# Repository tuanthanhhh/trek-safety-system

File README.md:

# Outdoor Safety Tracker System
> A Personal Outdoor Safety Tracker designed for trekking and remote activities, featuring fall detection, GPS tracking, environmental sensing, and LoRa-based emergency communication for real-time user monitoring.

## 📌 Overview
This project implements a handheld embedded system that enhances user safety during outdoor activities such as trekking, hiking, or exploration in remote areas.

The system continuously monitors user status and environment, detects abnormal conditions (e.g., fall or unconsciousness), and transmits alerts to a central monitoring station via LoRa communication.

## 🎯 Key Features
- Fall detection
- Lora Communication
- GPS Tracking
- Environmental Monitoring
- Digital Compass
- Emergency SOS

## 🏗️ System Architecture
🚧 Work in progress

## 🔧 Hardware Components
🚧 Work in progress
## 🧠 Software Design

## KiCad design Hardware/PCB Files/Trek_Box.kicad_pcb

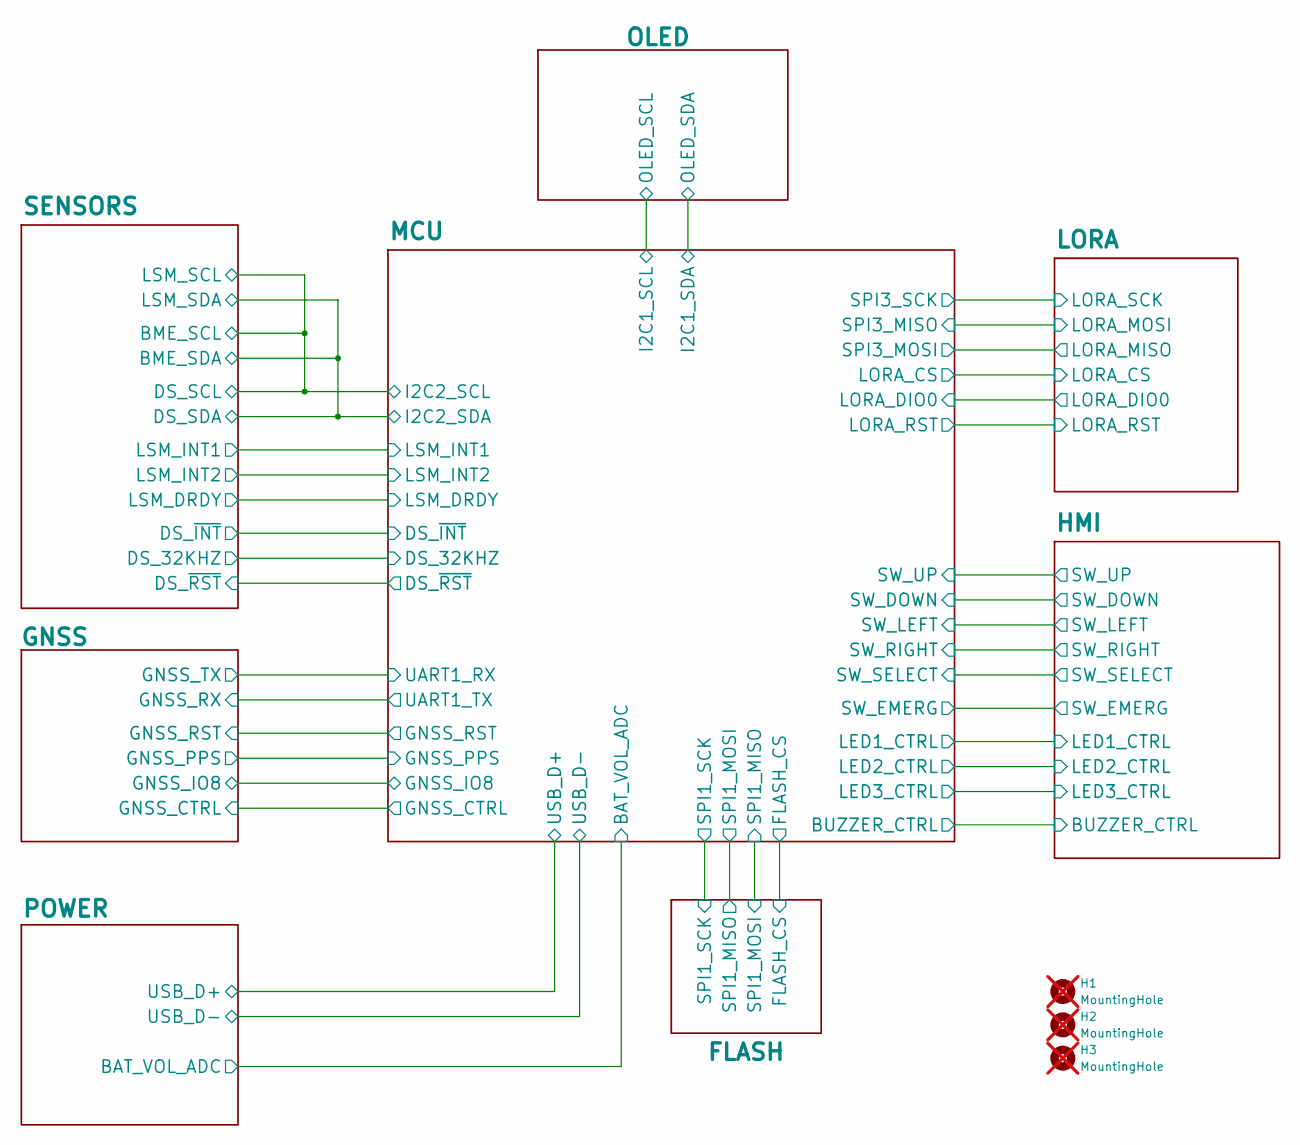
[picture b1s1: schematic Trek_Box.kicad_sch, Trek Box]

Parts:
H1, H2, H3: MountingHole; MountingHole_2.5mm; not fitted

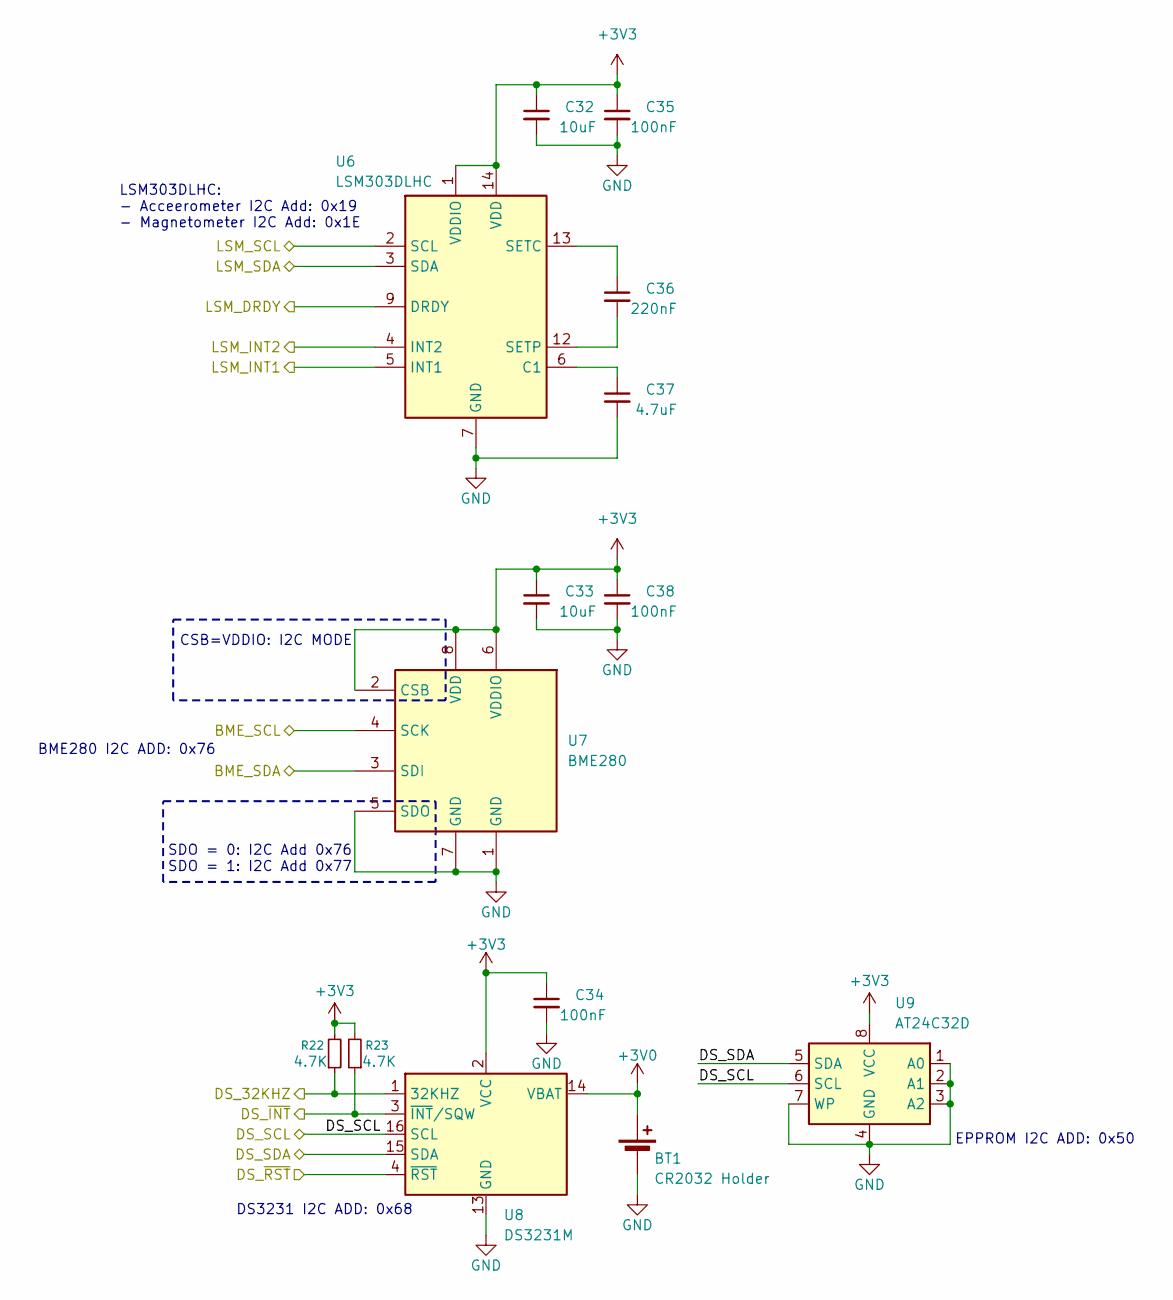
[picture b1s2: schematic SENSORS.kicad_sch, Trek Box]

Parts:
BT1: CR2032 Holder; BatteryHolder_Keystone_1060_1x2032
C32, C33: 10uF; C_0603_1608Metric; JLC C19702
C34, C35, C38: 100nF; C_0603_1608Metric; JLC C19702
C36: 220nF; C_0603_1608Metric; JLC C19702
C37: 4.7uF; C_0603_1608Metric; JLC C19702
R22, R23: 4.7K; R_0603_1608Metric
U6: LSM303DLHC; LGA-14_3x5mm_P0.8mm_LayoutBorder1x6y
U7: BME280; Bosch_LGA-8_2.5x2.5mm_P0.65mm_ClockwisePinNumbering
U8: DS3231M; SOIC-16W_7.5x10.3mm_P1.27mm
U9: AT24C32D; SOIC-8_3.9x4.9mm_P1.27mm

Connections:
+3V0: BT1.1 (+), U8.14 (VBAT); also elsewhere on the board
+3V3: C32.1, C33.1, C34.1, C35.1, C38.1, R22.2, R23.2, U6.1 (VDDIO), U6.14 (VDD), U7.2 (CSB), U7.6 (VDDIO), U7.8 (VDD), U8.2 (VCC), U9.8 (VCC); also elsewhere on the board
/MCU/DS_32KHZ: R22.1, U8.1 (32KHZ); also elsewhere on the board
/MCU/DS_~INT: R23.1, U8.3 (~INT/SQW); also elsewhere on the board
/MCU/DS_~RST: U8.4 (~RST); also elsewhere on the board
/MCU/I2C2_SCL: U6.2 (SCL), U7.4 (SCK), U8.16 (SCL), U9.6 (SCL); also elsewhere on the board
/MCU/I2C2_SDA: U6.3 (SDA), U7.3 (SDI), U8.15 (SDA), U9.5 (SDA); also elsewhere on the board
/MCU/LSM_DRDY: U6.9 (DRDY); also elsewhere on the board
/MCU/LSM_INT1: U6.5 (INT1); also elsewhere on the board
/MCU/LSM_INT2: U6.4 (INT2); also elsewhere on the board
GND: BT1.2 (-), C32.2, C33.2, C34.2, C35.2, C37.2, C38.2, U6.7 (GND), U6.10 (GND), U6.11 (GND), U7.1 (GND), U7.5 (SDO), U7.7 (GND), U8.5 (GND), U8.6 (GND), U8.7 (GND), U8.8 (GND), U8.9 (GND), U8.10 (GND), U8.11 (GND), U8.12 (GND), U8.13 (GND), U9.1 (A0), U9.2 (A1), U9.3 (A2), U9.4 (GND), U9.7 (WP); also elsewhere on the board
unnamed: C37.1, U6.6 (C1)
unnamed: C36.1, U6.13 (SETC)
unnamed: C36.2, U6.12 (SETP)

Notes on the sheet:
BME280 I2C ADD: 0x76
LSM303DLHC: - Acceerometer I2C Add: 0x19 - Magnetometer I2C Add: 0x1E
DS3231 I2C ADD: 0x68
SDO = 0: I2C Add 0x76 SDO = 1: I2C Add 0x77
CSB=VDDIO: I2C MODE
EPPROM I2C ADD: 0x50

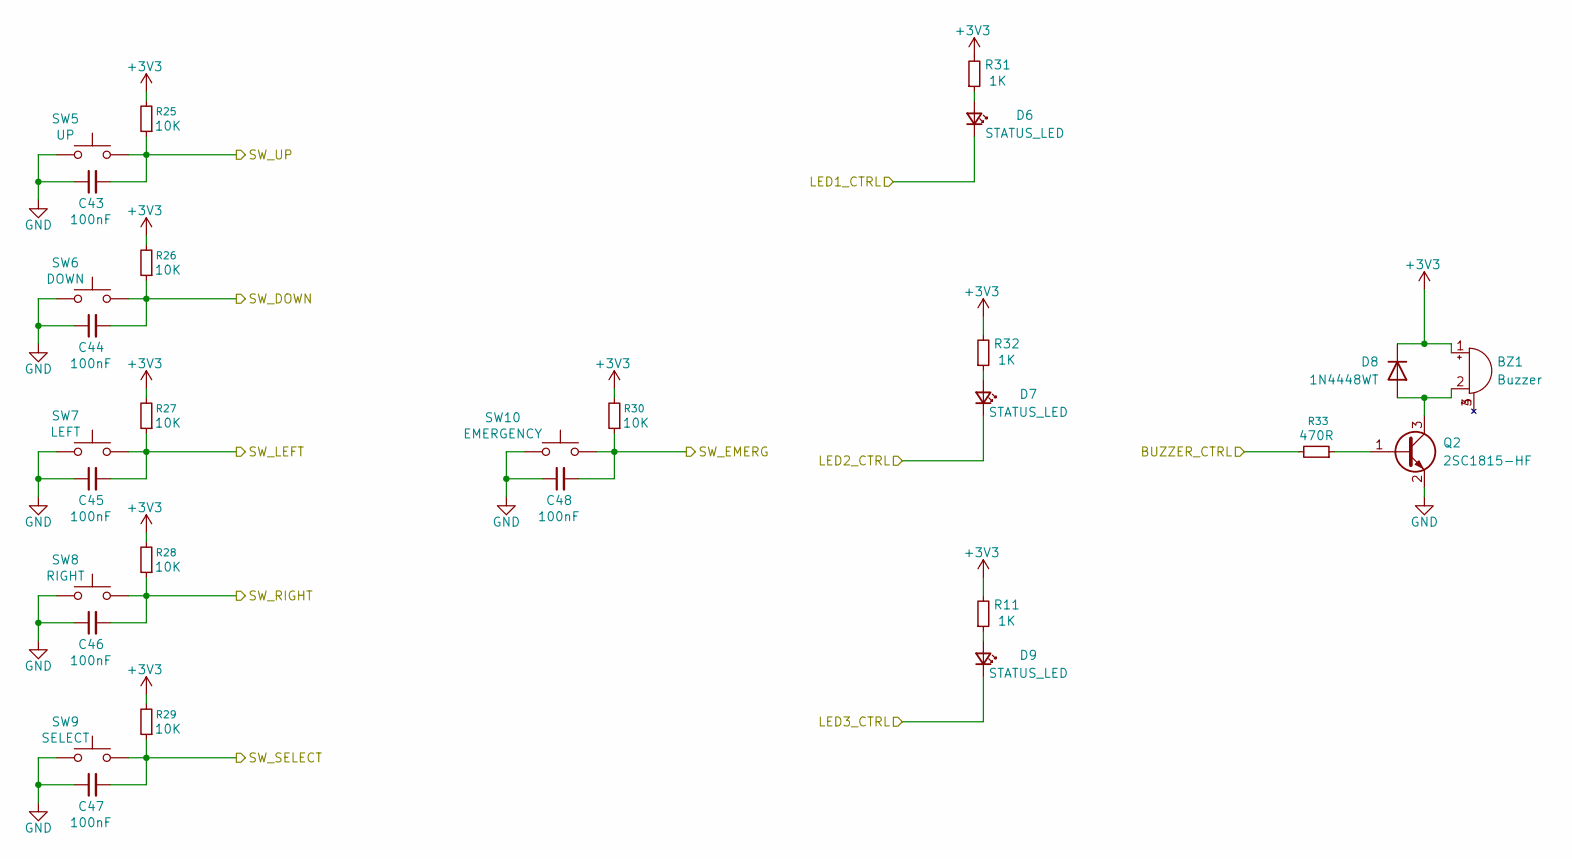
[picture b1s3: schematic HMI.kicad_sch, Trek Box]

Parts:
BZ1: Buzzer; Buzzer_8530
C43, C44, C45, C46, C47, C48: 100nF; C_0603_1608Metric
D6, D7, D9: STATUS_LED; LED_0603_1608Metric; JLC C2286
D8: 1N4448WT; D_SOD-523
Q2: 2SC1815-HF; SOT-23
R11, R31, R32: 1K; R_0603_1608Metric
R25, R26, R27, R28, R29, R30: 10K; R_0603_1608Metric
R33: 470R; R_0603_1608Metric
SW5: UP; SW_SPST_PTS647_Sx38
SW6: DOWN; SW_SPST_PTS647_Sx38
SW7: LEFT; SW_SPST_PTS647_Sx38
SW8: RIGHT; SW_SPST_PTS647_Sx38
SW9: SELECT; SW_SPST_PTS647_Sx38
SW10: EMERGENCY; SW_Tactile_SPST_Angled_PTS645Vx58-2LFS

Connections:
+3V3: BZ1.1 (+), D8.1 (K), R11.2, R25.2, R26.2, R27.2, R28.2, R29.2, R30.2, R31.2, R32.2; also elsewhere on the board
/HMI/BUZZER_CTRL: R33.2; also elsewhere on the board
/HMI/LED1_CTRL: D6.1 (K); also elsewhere on the board
/HMI/LED2_CTRL: D7.1 (K); also elsewhere on the board
/HMI/LED3_CTRL: D9.1 (K); also elsewhere on the board
/HMI/SW_DOWN: C44.2, R26.1, SW6.1; also elsewhere on the board
/HMI/SW_EMERG: C48.2, R30.1, SW10.1; also elsewhere on the board
/HMI/SW_LEFT: C45.2, R27.1, SW7.1; also elsewhere on the board
/HMI/SW_RIGHT: C46.2, R28.1, SW8.1; also elsewhere on the board
/HMI/SW_SELECT: C47.2, R29.1, SW9.1; also elsewhere on the board
/HMI/SW_UP: C43.2, R25.1, SW5.1; also elsewhere on the board
GND: C43.1, C44.1, C45.1, C46.1, C47.1, C48.1, Q2.2 (E), SW5.2, SW6.2, SW7.2, SW8.2, SW9.2, SW10.2; also elsewhere on the board
unnamed: BZ1.2 (-), D8.2 (A), Q2.3 (C)
unnamed: D6.2 (A), R31.1
unnamed: D7.2 (A), R32.1
unnamed: D9.2 (A), R11.1
unnamed: Q2.1 (B), R33.1

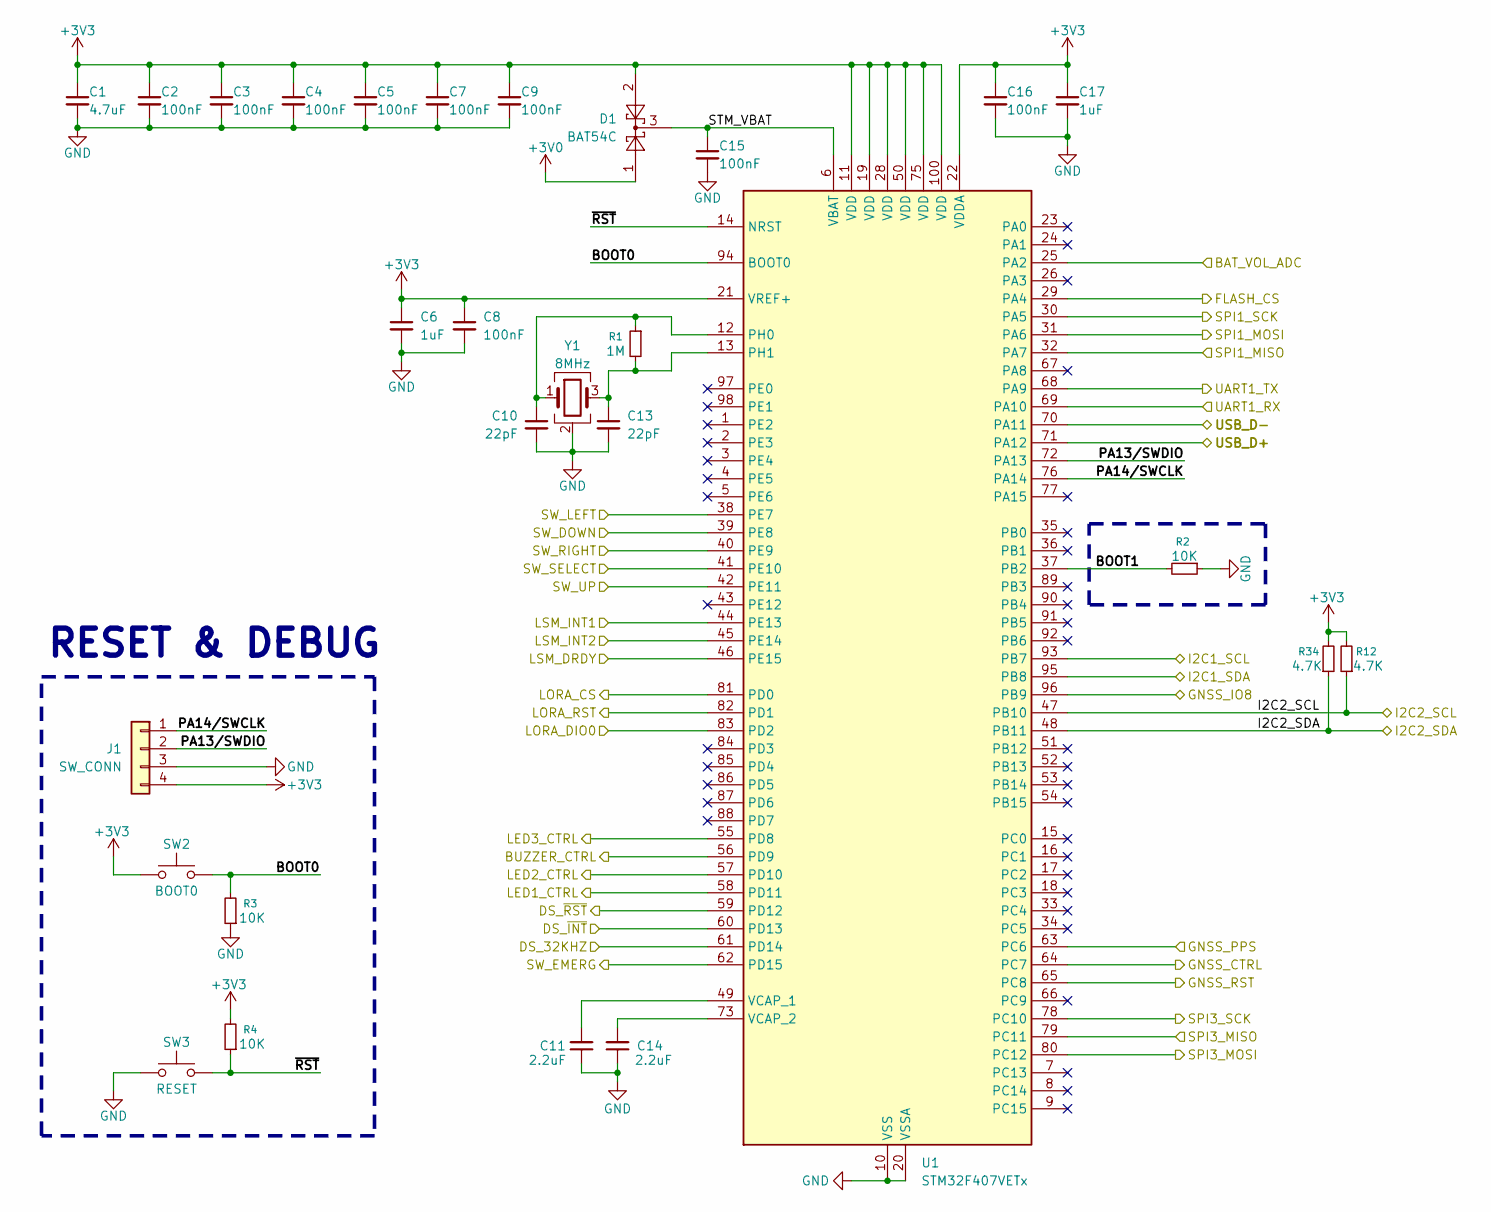
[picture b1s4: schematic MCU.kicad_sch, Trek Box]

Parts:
C1: 4.7uF; C_0603_1608Metric
C2, C3, C4, C5, C7, C8, C9, C15, C16: 100nF; C_0603_1608Metric
C6, C17: 1uF; C_0603_1608Metric
C10, C13: 22pF; C_0603_1608Metric
C11, C14: 2.2uF; C_0603_1608Metric
D1: BAT54C; SOT-23
J1: SW_CONN; PinHeader_1x04_P2.54mm_Vertical
R1: 1M; R_0603_1608Metric
R2, R3, R4: 10K; R_0603_1608Metric
R12, R34: 4.7K; R_0603_1608Metric
SW2: BOOT0; SW_SPST_PTS647_Sx38
SW3: RESET; SW_SPST_PTS647_Sx38
U1: STM32F407VETx; LQFP-100_14x14mm_P0.5mm
Y1: 8MHz; Crystal_SMD_3225-4Pin_3.2x2.5mm

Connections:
+3V0: D1.1; also elsewhere on the board
+3V3: C1.1, C2.1, C3.1, C4.1, C5.1, C6.1, C7.1, C8.1, C9.1, C16.1, C17.1, D1.2, J1.4, R4.2, R12.2, R34.2, SW2.2, U1.11 (VDD), U1.19 (VDD), U1.21 (VREF+), U1.22 (VDDA), U1.28 (VDD), U1.50 (VDD), U1.75 (VDD), U1.100 (VDD); also elsewhere on the board
/FLASH/FLASH_CS: U1.29 (PA4); also elsewhere on the board
/FLASH/SPI1_MISO: U1.31 (PA6); also elsewhere on the board
/FLASH/SPI1_MOSI: U1.32 (PA7); also elsewhere on the board
/FLASH/SPI1_SCK: U1.30 (PA5); also elsewhere on the board
/GNSS/GNSS_CTRL: U1.64 (PC7); also elsewhere on the board
/GNSS/GNSS_IO8: U1.96 (PB9); also elsewhere on the board
/GNSS/GNSS_PPS: U1.63 (PC6); also elsewhere on the board
/GNSS/GNSS_RST: U1.65 (PC8); also elsewhere on the board
/GNSS/GNSS_RX: U1.68 (PA9); also elsewhere on the board
/GNSS/GNSS_TX: U1.69 (PA10); also elsewhere on the board
/HMI/BUZZER_CTRL: U1.56 (PD9); also elsewhere on the board
/HMI/LED1_CTRL: U1.58 (PD11); also elsewhere on the board
/HMI/LED2_CTRL: U1.57 (PD10); also elsewhere on the board
/HMI/LED3_CTRL: U1.55 (PD8); also elsewhere on the board
/HMI/SW_DOWN: U1.39 (PE8); also elsewhere on the board
/HMI/SW_EMERG: U1.62 (PD15); also elsewhere on the board
/HMI/SW_LEFT: U1.38 (PE7); also elsewhere on the board
/HMI/SW_RIGHT: U1.40 (PE9); also elsewhere on the board
/HMI/SW_SELECT: U1.41 (PE10); also elsewhere on the board
/HMI/SW_UP: U1.42 (PE11); also elsewhere on the board
/LORA/LORA_CS: U1.81 (PD0); also elsewhere on the board
/LORA/LORA_INT: U1.83 (PD2); also elsewhere on the board
/LORA/LORA_MISO: U1.80 (PC12); also elsewhere on the board
/LORA/LORA_MOSI: U1.79 (PC11); also elsewhere on the board
/LORA/LORA_RST: U1.82 (PD1); also elsewhere on the board
/LORA/LORA_SCK: U1.78 (PC10); also elsewhere on the board
/MCU/BAT_VOL_ADC: U1.25 (PA2); also elsewhere on the board
/MCU/BOOT0: R3.2, SW2.1, U1.94 (BOOT0)
/MCU/BOOT1: R2.2, U1.37 (PB2)
/MCU/DS_32KHZ: U1.61 (PD14); also elsewhere on the board
/MCU/DS_~INT: U1.60 (PD13); also elsewhere on the board
/MCU/DS_~RST: U1.59 (PD12); also elsewhere on the board
/MCU/I2C1_SCL: U1.93 (PB7); also elsewhere on the board
/MCU/I2C1_SDA: U1.95 (PB8); also elsewhere on the board
/MCU/I2C2_SCL: R12.1, U1.47 (PB10); also elsewhere on the board
/MCU/I2C2_SDA: R34.1, U1.48 (PB11); also elsewhere on the board
/MCU/LSM_DRDY: U1.46 (PE15); also elsewhere on the board
/MCU/LSM_INT1: U1.44 (PE13); also elsewhere on the board
/MCU/LSM_INT2: U1.45 (PE14); also elsewhere on the board
/MCU/PA13/SWDIO: J1.2, U1.72 (PA13)
/MCU/PA14/SWCLK: J1.1, U1.76 (PA14)
/MCU/STM_VBAT: C15.1, D1.3, U1.6 (VBAT)
/MCU/~RST: R4.1, SW3.1, U1.14 (NRST)
/POWER/USB_D+: U1.71 (PA12); also elsewhere on the board
/POWER/USB_D-: U1.70 (PA11); also elsewhere on the board
GND: C1.2, C2.2, C3.2, C4.2, C5.2, C6.2, C7.2, C8.2, C9.2, C10.2, C11.1, C13.2, C14.1, C15.2, C16.2, C17.2, J1.3, R2.1, R3.1, SW3.2, U1.10 (VSS), U1.20 (VSSA), U1.27 (VSS), U1.74 (VSS), U1.99 (VSS), Y1.2 (G), Y1.4 (G); also elsewhere on the board
unnamed: C10.1, R1.1, U1.12 (PH0), Y1.1
unnamed: C13.1, R1.2, U1.13 (PH1), Y1.3
unnamed: C11.2, U1.49 (VCAP_1)
unnamed: C14.2, U1.73 (VCAP_2)

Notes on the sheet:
RESET & DEBUG

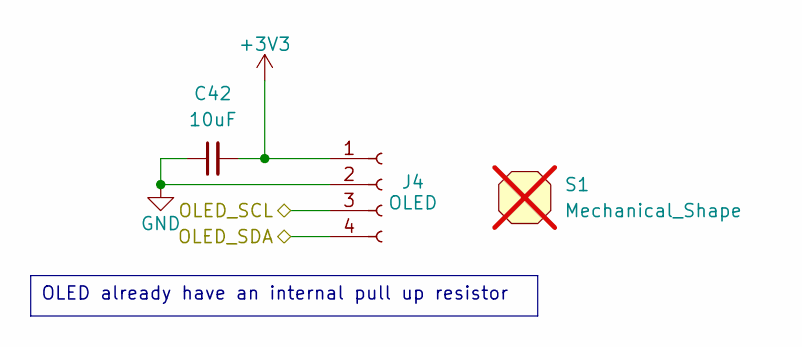
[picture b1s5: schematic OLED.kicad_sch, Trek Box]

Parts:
C42: 10uF; C_0603_1608Metric
J4: OLED; PinHeader_1x04_P2.54mm_Vertical
S1: Mechanical_Shape; OLED_1inch3; not fitted

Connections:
+3V3: C42.2, J4.1; also elsewhere on the board
/MCU/I2C1_SCL: J4.3; also elsewhere on the board
/MCU/I2C1_SDA: J4.4; also elsewhere on the board
GND: C42.1, J4.2; also elsewhere on the board

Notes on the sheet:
OLED already have an internal pull up resistor

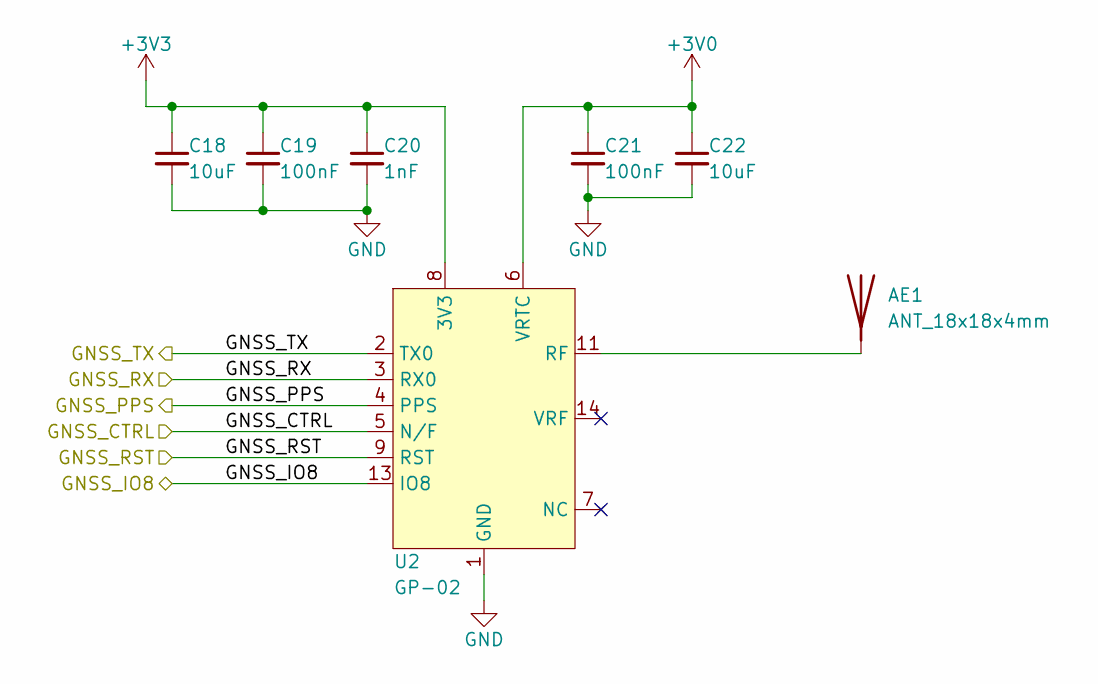
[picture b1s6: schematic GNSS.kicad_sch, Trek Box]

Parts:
AE1: ANT_18x18x4mm; PATH_ANT_18x18x4mm
C18, C22: 10uF; C_0603_1608Metric
C19, C21: 100nF; C_0603_1608Metric
C20: 1nF; C_0603_1608Metric
U2: GP-02; GP-02_FULL_PAD

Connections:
+3V0: C21.1, C22.1, U2.6 (VRTC); also elsewhere on the board
+3V3: C18.1, C19.1, C20.1, U2.8 (3V3); also elsewhere on the board
/GNSS/GNSS_CTRL: U2.5 (N/F); also elsewhere on the board
/GNSS/GNSS_IO8: U2.13 (IO8); also elsewhere on the board
/GNSS/GNSS_PPS: U2.4 (PPS); also elsewhere on the board
/GNSS/GNSS_RST: U2.9 (RST); also elsewhere on the board
/GNSS/GNSS_RX: U2.3 (RX0); also elsewhere on the board
/GNSS/GNSS_TX: U2.2 (TX0); also elsewhere on the board
GND: C18.2, C19.2, C20.2, C21.2, C22.2, U2.1 (GND), U2.10 (GND), U2.12 (GND); also elsewhere on the board
unnamed: AE1.1 (A_1), U2.11 (RF)

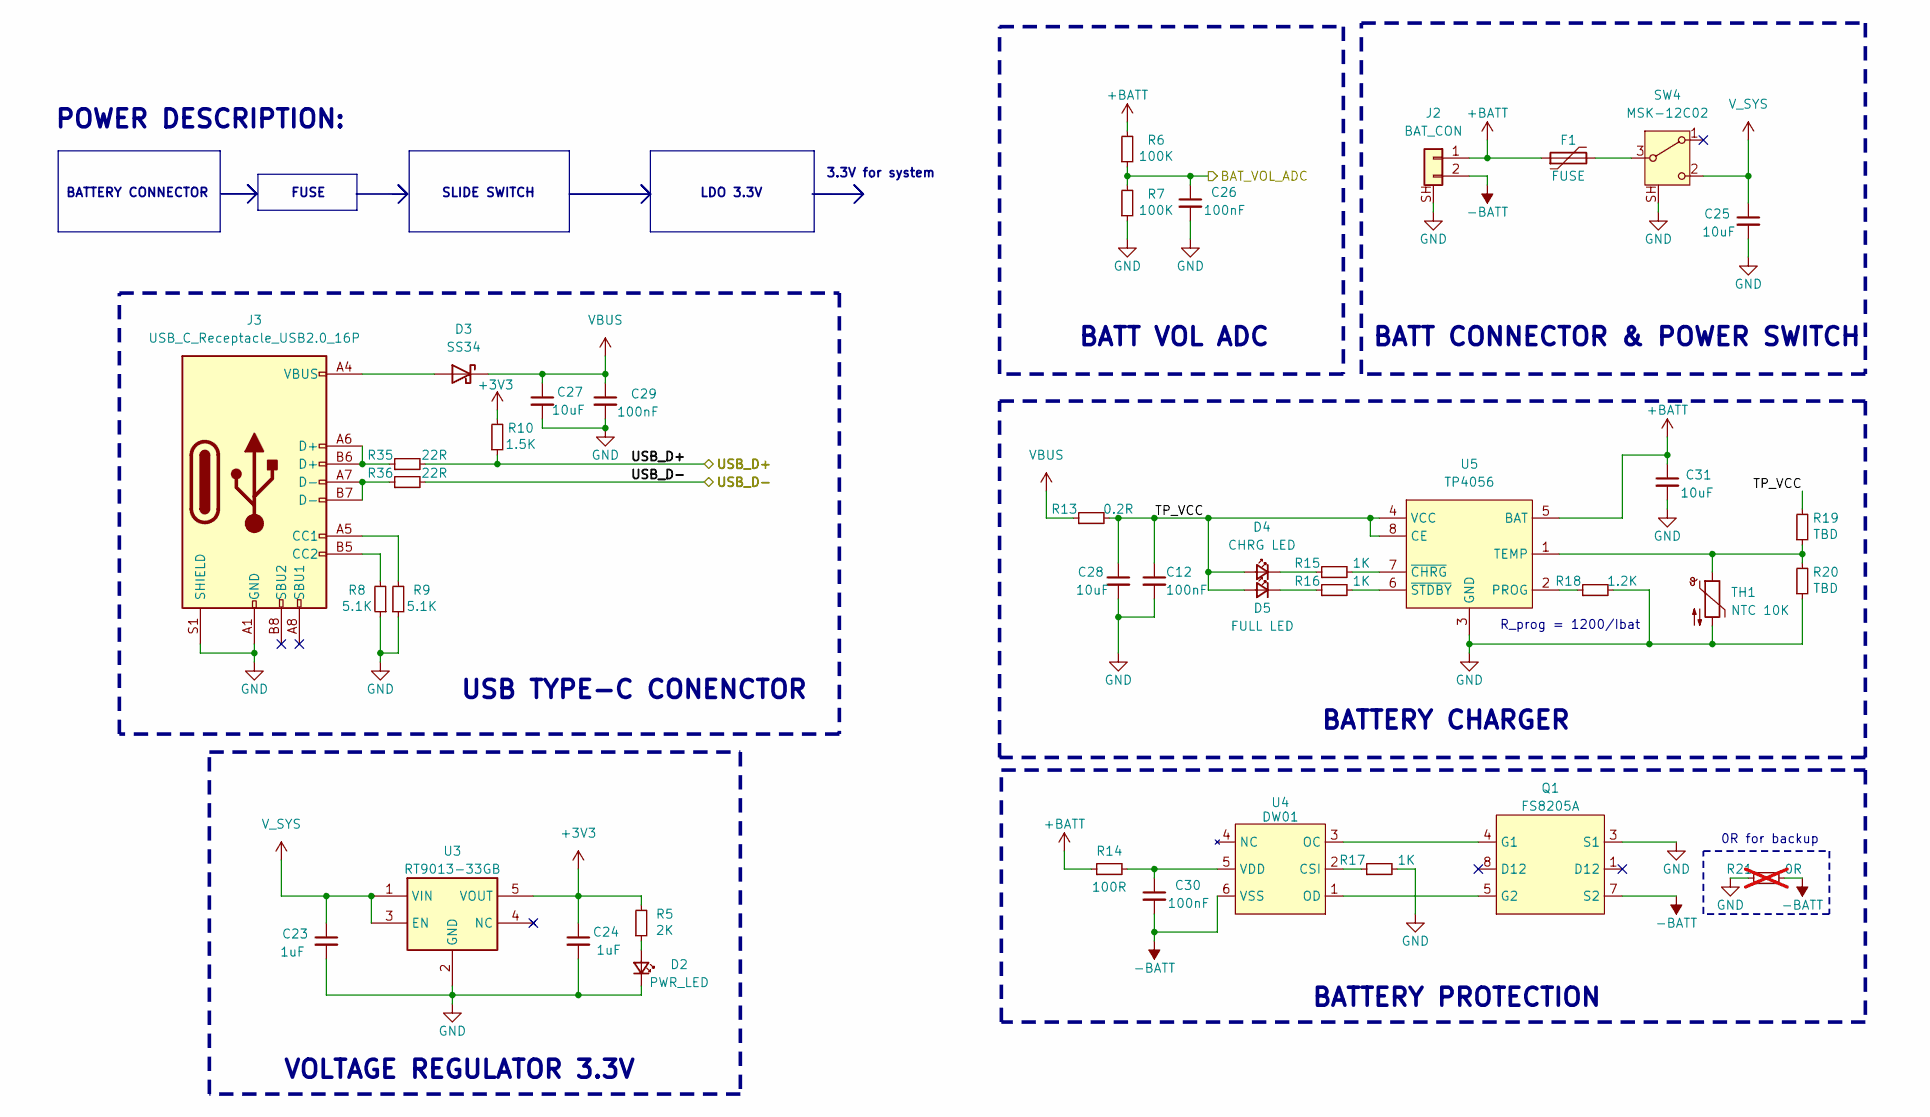
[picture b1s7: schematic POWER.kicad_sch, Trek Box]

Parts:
C12: 100nF; C_0603_1608Metric
C23, C24: 1uF; C_0603_1608Metric; JLC C19702
C25, C31: 10uF; C_0603_1608Metric; JLC C19702
C26, C30: 100nF; C_0603_1608Metric; JLC C1590
C27, C28: 10uF; C_0805_2012Metric
C29: 100nF; C_0603_1608Metric; JLC C19702
D2: PWR_LED; LED_0603_1608Metric; JLC C2286
D3: SS34; D_SMA
D4: CHRG LED; LED_0603_1608Metric; JLC C2286
D5: FULL LED; LED_0603_1608Metric; JLC C22371299
F1: FUSE; Fuse_0805_2012Metric; JLC C720076
J2: BAT_CON; CON_XH_254_R_SMD
J3: USB_C_Receptacle_USB2.0_16P; USB_C_Receptacle_GCT_USB4105-xx-A_16P_TopMnt_Horizontal
Q1: FS8205A; TSSOP-8_4.4x3mm_P0.65mm
R5: 2K; R_0603_1608Metric
R6, R7: 100K; R_0603_1608Metric
R8, R9: 5.1K; R_0603_1608Metric
R10: 1.5K; R_0603_1608Metric
R13: 0.2R; R_1206_3216Metric
R14: 100R; R_0603_1608Metric
R15, R16, R17: 1K; R_0603_1608Metric; JLC C22548
R18: 1.2K; R_0603_1608Metric; JLC C22765
R19, R20: TBD; R_0603_1608Metric
R21: 0R; R_0603_1608Metric; not fitted
R35, R36: 22R; R_0402_1005Metric
SW4: MSK-12C02; SW_SPDT_Shouhan_MSK12C02; JLC C963206
TH1: NTC 10K; R_0603_1608Metric
U3: RT9013-33GB; SOT-23-5
U4: DW01; SOT-23-6; JLC C917079
U5: TP4056; SOIC127P600X175-9N; JLC C725790

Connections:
+3V3: C24.1, R5.2, R10.2, U3.5 (VOUT); also elsewhere on the board
+BATT: C31.1, F1.1, J2.1, R6.2, R14.1, U5.5 (BAT)
-BATT: C30.2, J2.2, Q1.6 (S2), Q1.7 (S2), R21.2, U4.6 (VSS)
/MCU/BAT_VOL_ADC: C26.1, R6.1, R7.2; also elsewhere on the board
/POWER/TP_VCC: C12.1, C28.1, D4.2 (A), D5.2 (A), R13.2, R19.2, U5.4 (VCC), U5.8 (CE)
/POWER/USB_D+: R10.1, R35.2; also elsewhere on the board
/POWER/USB_D-: R36.2; also elsewhere on the board
GND: C12.2, C23.2, C24.2, C25.2, C26.2, C27.2, C28.2, C29.2, C31.2, D2.1 (K), J2.SH, J3.A1 (GND), J3.A12 (GND), J3.B1 (GND), J3.B12 (GND), J3.S1 (SHIELD), Q1.2 (S1), Q1.3 (S1), R7.1, R8.1, R9.1, R17.2, R18.2, R20.1, R21.1, SW4.SH, TH1.2, U3.2 (GND), U5.3 (GND), U5.9 (EPAD); also elsewhere on the board
unnamed: D2.2 (A), R5.1
unnamed: D3.2 (A), J3.A4 (VBUS), J3.A9 (VBUS), J3.B4 (VBUS), J3.B9 (VBUS)
unnamed: D4.1 (K), R15.1
unnamed: D5.1 (K), R16.1
unnamed: J3.A5 (CC1), R9.2
unnamed: J3.B5 (CC2), R8.2
unnamed: J3.A6 (D+), J3.B6 (D+), R35.1
unnamed: J3.A7 (D-), J3.B7 (D-), R36.1
unnamed: Q1.4 (G1), U4.3 (OC)
unnamed: Q1.5 (G2), U4.1 (OD)
unnamed: F1.2, SW4.3 (A)
unnamed: R17.1, U4.2 (CSI)
unnamed: C30.1, R14.2, U4.5 (VDD)
unnamed: R18.1, U5.2 (PROG)
unnamed: R19.1, R20.2, TH1.1, U5.1 (TEMP)
unnamed: R15.2, U5.7 (~CHRG)
unnamed: R16.2, U5.6 (~STDBY)
VBUS: C27.1, C29.1, D3.1 (K), R13.1
V_SYS: C23.1, C25.1, SW4.2 (C), U3.1 (VIN), U3.3 (EN)

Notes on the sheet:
VOLTAGE REGULATOR 3.3V
BATT CONNECTOR & POWER SWITCH
BATTERY PROTECTION
USB TYPE-C CONENCTOR
FUSE
0R for backup
3.3V for system
POWER DESCRIPTION:
LDO 3.3V
SLIDE SWITCH
BATTERY CONNECTOR
BATTERY CHARGER
BATT VOL ADC
R_prog = 1200/Ibat

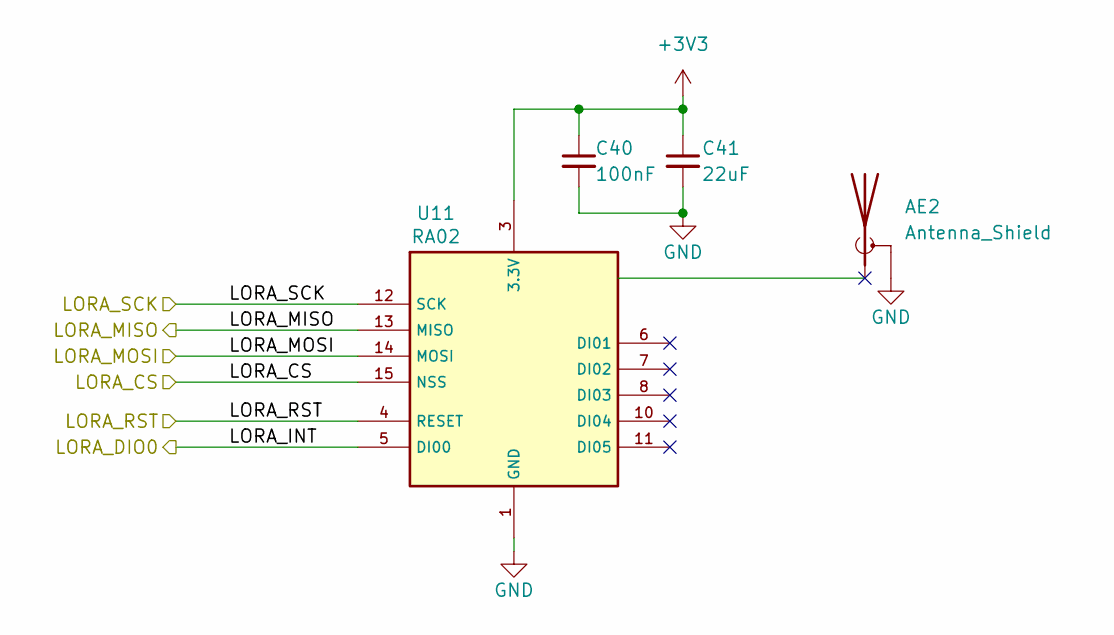
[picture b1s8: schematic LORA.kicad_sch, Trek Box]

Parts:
AE2: Antenna_Shield; SMA_Molex_73251-2200_Horizontal
C40: 100nF; C_0603_1608Metric
C41: 22uF; C_0805_2012Metric
U11: RA02; RA-02

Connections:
+3V3: C40.1, C41.1, U11.3 (3.3V); also elsewhere on the board
/LORA/LORA_CS: U11.15 (NSS); also elsewhere on the board
/LORA/LORA_INT: U11.5 (DI00); also elsewhere on the board
/LORA/LORA_MISO: U11.13 (MISO); also elsewhere on the board
/LORA/LORA_MOSI: U11.14 (MOSI); also elsewhere on the board
/LORA/LORA_RST: U11.4 (RESET); also elsewhere on the board
/LORA/LORA_SCK: U11.12 (SCK); also elsewhere on the board
GND: AE2.2 (Shield_2), C40.2, C41.2, U11.1 (GND), U11.2 (GND), U11.9 (GND), U11.16 (GND); also elsewhere on the board

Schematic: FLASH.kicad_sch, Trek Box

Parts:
C39: 100nF; C_0603_1608Metric
R24: 10K; R_0603_1608Metric
U10: W25Q32JVSS; SOIC-8_5.3x5.3mm_P1.27mm

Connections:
+3V3: C39.1, R24.1, U10.3 (~WP/IO_{2}), U10.7 (~HOLD/~RESET/IO_{3}), U10.8 (VCC); also elsewhere on the board
/FLASH/FLASH_CS: R24.2, U10.1 (~CS); also elsewhere on the board
/FLASH/SPI1_MISO: U10.2 (DO/IO_{1}); also elsewhere on the board
/FLASH/SPI1_MOSI: U10.5 (DI/IO_{0}); also elsewhere on the board
/FLASH/SPI1_SCK: U10.6 (CLK); also elsewhere on the board
GND: C39.2, U10.4 (GND); also elsewhere on the board

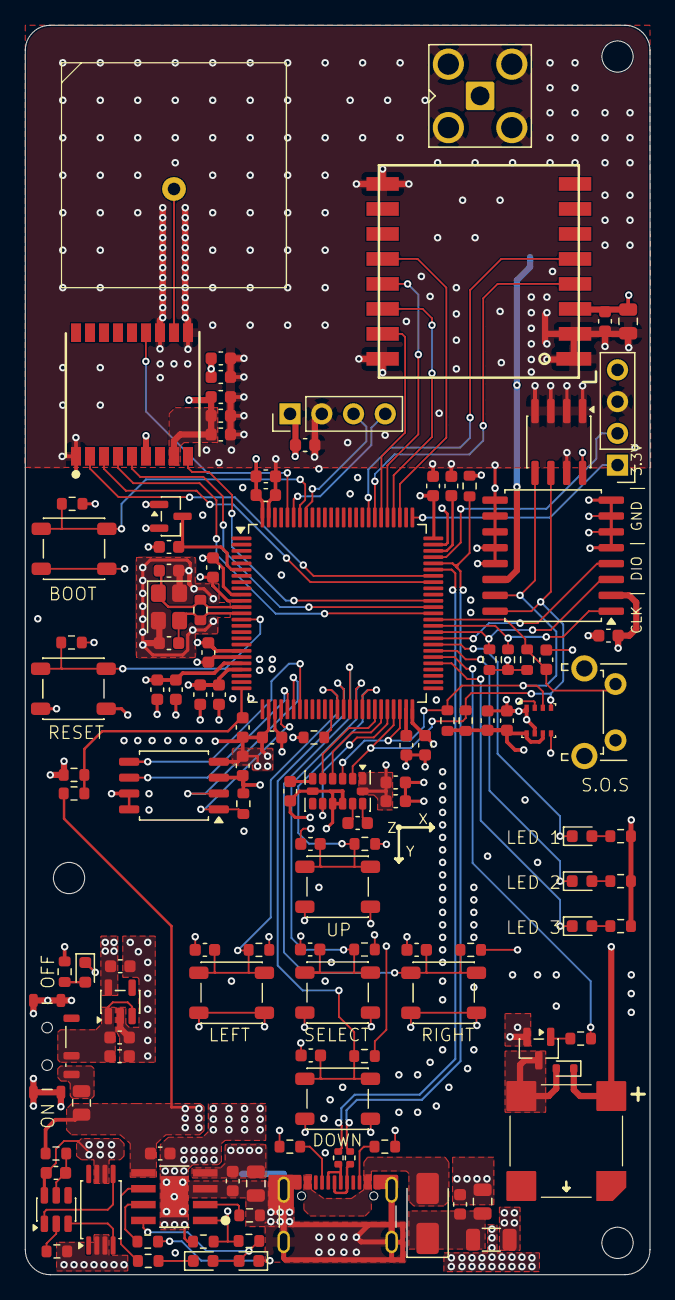
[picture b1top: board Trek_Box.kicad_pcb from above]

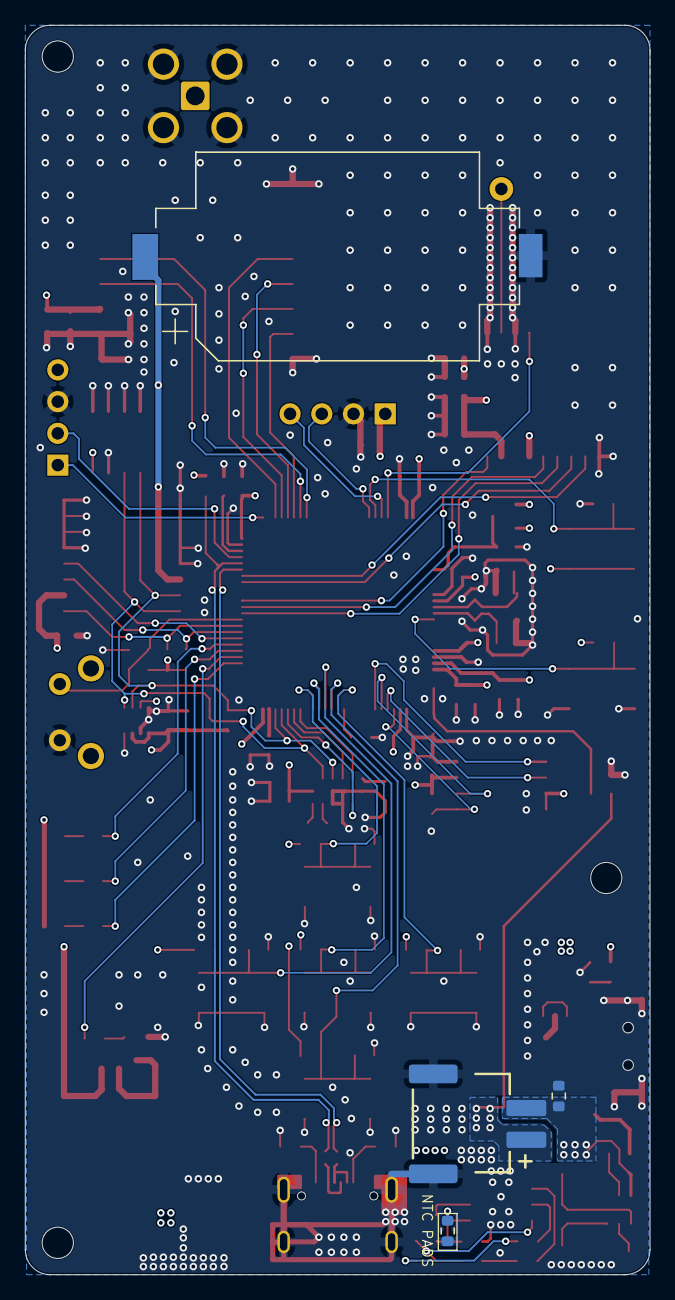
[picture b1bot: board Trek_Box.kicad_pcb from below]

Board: 4 copper layers, 50.0 x 100.0 mm, 130 parts (4 on the bottom side), 83 nets.

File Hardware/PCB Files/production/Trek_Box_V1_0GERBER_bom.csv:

Designator,Footprint,Quantity,Value,LCSC Part #
AE1,PATH_ANT_18x18x4mm,1,ANT_18x18x4mm,
AE2,SMA_Amphenol_901-143_Horizontal,1,Antenna_Shield,
BT1,BatteryHolder_Keystone_1060_1x2032,1,CR2032 Holder,
BZ1,Buzzer_8530,1,Buzzer,
C1,0603,1,4.7uF,
"C10, C13",0603,2,22pF,
"C11, C14",0603,2,2.2uF,
"C12, C15, C16, C19, C2, C21, C3, C39, C4, C40, C43, C44, C45, C46, C47, C48, C5, C7, C8, C9",0603,20,100nF,
"C17, C6",0603,2,1uF,
"C18, C22, C42",0603,3,10uF,
C20,0603,1,1nF,
"C23, C24",0603,2,1uF,C19702
"C25, C31, C32, C33",0603,4,10uF,C19702
"C26, C30",0603,2,100nF,C1590
"C27, C28",0805,2,10uF,
"C29, C34, C35, C38",0603,4,100nF,C19702
C36,0603,1,220nF,C19702
C37,0603,1,4.7uF,C19702
C41,0805,1,22uF,
D1,SOT-23,1,BAT54C,
D2,0603,1,PWR_LED,C2286
D3,D_SMA,1,SS34,
D4,0603,1,CHRG LED,C2286
D5,0603,1,FULL LED,C22371299
"D6, D7, D9",0603,3,STATUS_LED,C2286
D8,D_SOD-523,1,1N4448WT,
F1,0805,1,FUSE,C720076
J1,PinHeader_1x04_P2.54mm_Vertical,1,SW_CONN,
J2,CON_XH_254_R_SMD,1,BAT_CON,
J3,USB_C_Receptacle_GCT_USB4105-xx-A_16P_TopMnt_Horizontal,1,USB_C_Receptacle_USB2.0_16P,
J4,PinHeader_1x04_P2.54mm_Vertical,1,OLED,
Q1,TSSOP-8_4.4x3mm_P0.65mm,1,FS8205A,
Q2,SOT-23,1,2SC1815-HF,
R1,0603,1,1M,
R10,0603,1,1.5K,
"R11, R31, R32",0603,3,1K,
"R12, R19, R20, R34",0603,4,TBD,
R13,1206,1,0.2R,
R14,0603,1,100R,
"R15, R16, R17",0603,3,1K,C22548
R18,0603,1,1.2K,C22765
"R2, R24, R25, R26, R27, R28, R29, R3, R30, R4",0603,10,10K,
"R22, R23",0603,2,4.7K,
R33,0603,1,470R,
"R35, R36",0402,2,22R,
R5,0603,1,2K,
"R6, R7",0603,2,100K,
"R8, R9",0603,2,5.1K,
SW10,SW_Tactile_SPST_Angled_PTS645Vx58-2LFS,1,EMERGENCY,
SW2,SW_SPST_PTS647_Sx38,1,BOOT0,
SW3,SW_SPST_PTS647_Sx38,1,RESET,
SW4,SW_SPDT_Shouhan_MSK12C02,1,MSK-12C02,C963206
SW5,SW_SPST_PTS647_Sx38,1,UP,
SW6,SW_SPST_PTS647_Sx38,1,DOWN,
SW7,SW_SPST_PTS647_Sx38,1,LEFT,
SW8,SW_SPST_PTS647_Sx38,1,RIGHT,
SW9,SW_SPST_PTS647_Sx38,1,SELECT,
TH1,0603,1,NTC 10K,
U1,LQFP-100_14x14mm_P0.5mm,1,STM32F407VETx,
U10,SOIC-8_5.3x5.3mm_P1.27mm,1,W25Q32JVSS,
U11,RA-02,1,RA02,
U2,GP-02_FULL_PAD,1,GP-02,
U3,SOT-23-5,1,RT9013-33GB,
U4,SOT-23-6,1,DW01,C917079
U5,SOIC127P600X175-9N,1,TP4056,C725790
U6,LGA-14_3x5mm_P0.8mm_LayoutBorder1x6y,1,LSM303DLHC,
U7,Bosch_LGA-8_2.5x2.5mm_P0.65mm_ClockwisePinNumbering,1,BME280,
U8,SOIC-16W_7.5x10.3mm_P1.27mm,1,DS3231M,
U9,SOIC-8_3.9x4.9mm_P1.27mm,1,AT24C32D,
Y1,Crystal_SMD_3225-4Pin_3.2x2.5mm,1,8MHz,

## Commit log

2026-05-03 init Trekking Safety Device Project
2026-05-03 Revise README for Outdoor Safety Tracker System
    Updated project title and added detailed overview and features.
2026-05-07 Reorganize repository structure
2026-05-07 Create Hardware folder and update PCB Files
2026-05-08 Update gitignore file
2026-05-08 Edited gitignore file and remove backup file
2026-05-08 Ignore History folder
2026-05-08 Added Readme
2026-05-16 split main application into functional modules
2026-05-18 Add STM32F407_BASE to Firmware_TRILE folder
2026-05-18 Xoa 3 thu muc STM32 du thua khoi nhanh main
2026-05-20 Enhance OLED UI and refine digital compass calculation
2026-05-30 fix digital compass and current time function
2026-05-31 Fix UI
2026-05-31 Fix SOS Signal
2026-06-06 Update Firmware_TRILE from local workspace
